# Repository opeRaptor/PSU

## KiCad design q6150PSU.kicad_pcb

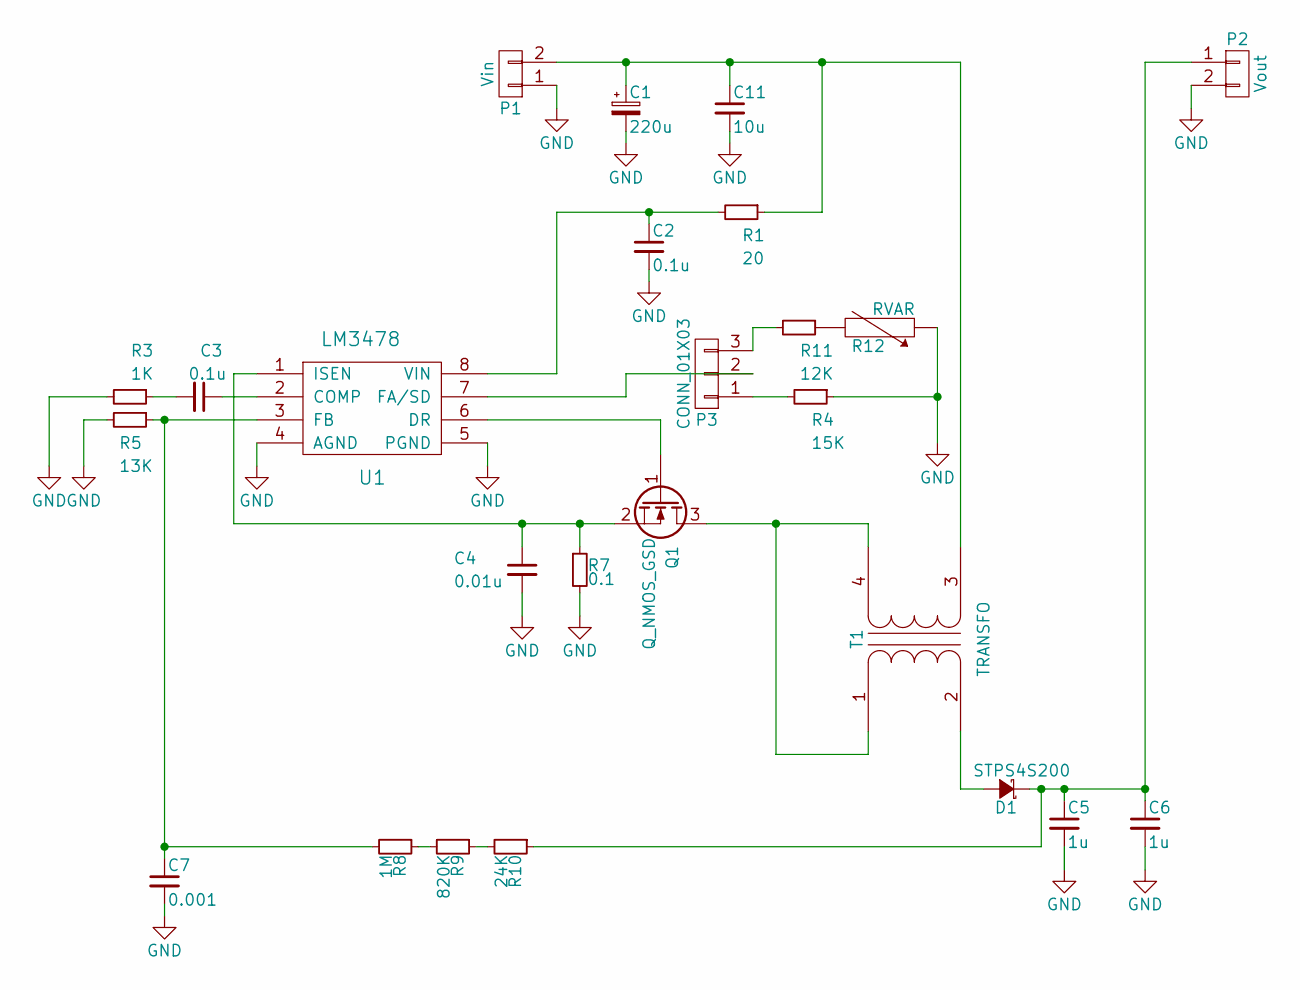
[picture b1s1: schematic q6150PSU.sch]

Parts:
C1: 220u; c_elec_6.3x7.7
C2, C3: 0.1u; C_0805_HandSoldering
C4: 0.01u; C_0805_HandSoldering
C5, C6: 1u; C_2220_HandSoldering
C7: 0.001; C_0805_HandSoldering
C11: 10u; C_0805_HandSoldering
D1: STPS4S200; SMB_Handsoldering
P1: Vin; Pin_Header_Straight_1x02
P2: Vout; Pin_Header_Straight_1x02
P3: CONN_01X03; Pin_Header_Straight_1x03
Q1: Q_NMOS_GSD; SOT-23_Handsoldering
R1: 20; R_0805_HandSoldering
R3: 1K; R_0805_HandSoldering
R4: 15K; R_0805_HandSoldering
R5: 13K; R_0805_HandSoldering
R7: 0.1; R_0805_HandSoldering
R8: 1M; R_0805_HandSoldering
R9: 820K; R_0805_HandSoldering
R10: 24K; R_0805_HandSoldering
R11: 12K; R_0805_HandSoldering
R12: RVAR; potsmd
T1: TRANSFO; CTX02-18714-R
U1: LM3478; SOIC-8-N

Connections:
GND: C1.2, C2.2, C4.2, C5.2, C6.2, C7.2, C11.2, P1.1, P2.2, R3.2, R4.1, R5.2, R7.2, R12.1, U1.4 (AGND), U1.5 (PGND)
unnamed: C1.1, C11.1, P1.2, R1.1, T1.3 (SA)
unnamed: C2.1, R1.2, U1.8 (VIN)
unnamed: C3.1, U1.2 (COMP)
unnamed: C3.2, R3.1
unnamed: C4.1, Q1.2 (S), R7.1, U1.1 (ISEN)
unnamed: C5.1, C6.1, D1.1 (K), P2.1, R10.1
unnamed: C7.1, R5.1, R8.2, U1.3 (FB)
unnamed: D1.2 (A), T1.2 (AB)
unnamed: P3.1, R4.2
unnamed: P3.2, U1.7 (FA/SD)
unnamed: P3.3, R11.2
unnamed: Q1.1 (G), U1.6 (DR)
unnamed: Q1.3 (D), T1.1 (AA), T1.4 (SB)
unnamed: R8.1, R9.2
unnamed: R9.1, R10.2
unnamed: R11.1, R12.2

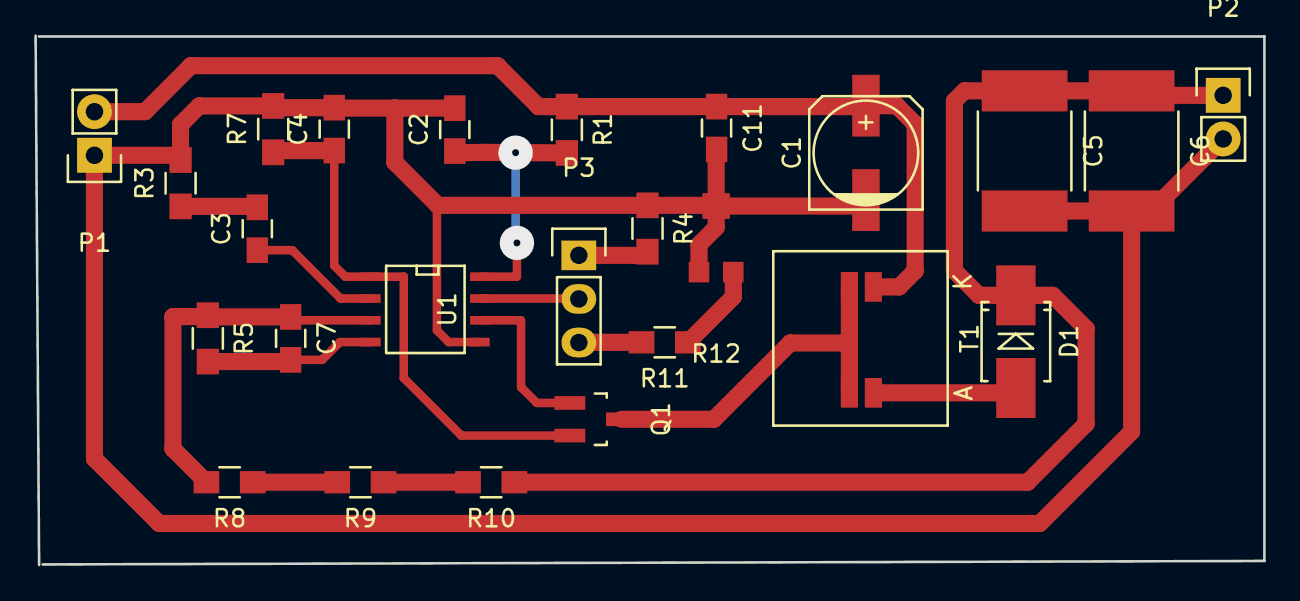
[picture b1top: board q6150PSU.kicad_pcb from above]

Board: 2 copper layers, 71.6 x 30.8 mm, 25 parts (0 on the bottom side), 17 nets.

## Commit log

2016-10-15 All layout + Pot
2016-10-30 Fixed and it works!
